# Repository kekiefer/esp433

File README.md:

# ESP433

KiCad source to build an ESP8266 WiFi to 433MHz ASK/OOK bridge

## How to Build One

This board is available on Oshpark: https://oshpark.com/shared_projects/5Debb7gg

The bom has been exported here as esp433.csv

## Key Components

* ESP12s - ESP8266 surface mount WiFi module
* Maxim MAX7044AKA+T - 300 ~ 450 MHz ASK/OOK RF transmitter
* Mean Well IRM-02-5 - AC to DC Power Supply 5V 2W
* PolyCase GS-2315 - Plug-in project enclosure

## More Information

A project writeup is available on hackaday.io: https://hackaday.io/project/63004-esp433-wifi-to-433mhz-bridge

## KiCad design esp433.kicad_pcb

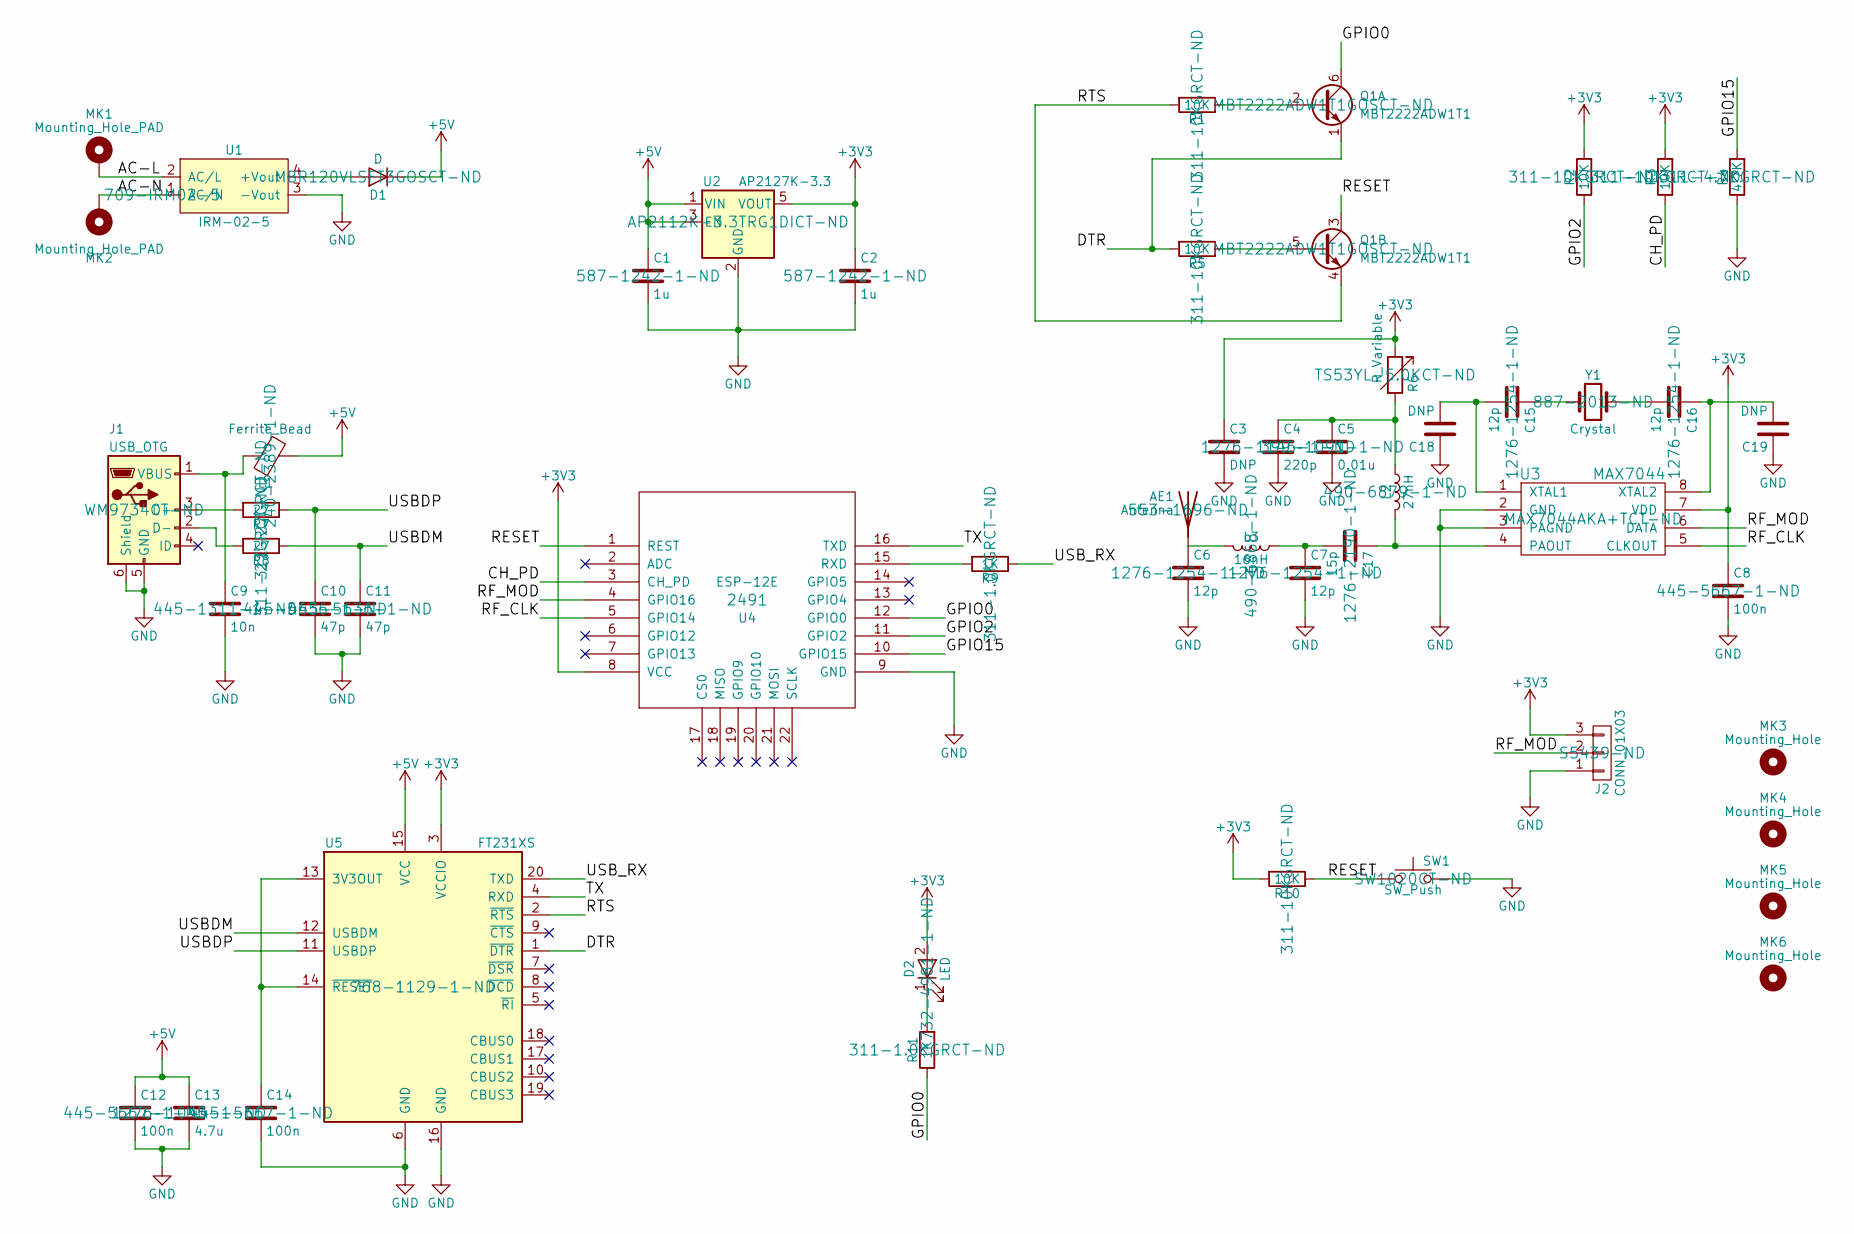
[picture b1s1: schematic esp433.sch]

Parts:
AE1: Antenna; W3127
C1, C2: 1u; C_0603
C3, C18, C19: DNP; C_0603
C4: 220p; C_0603
C5: 0.01u; C_0603
C6, C7, C15, C16: 12p; C_0603
C8, C12, C14: 100n; C_0603
C9: 10n; C_0603
C10, C11: 47p; C_0603
C13: 4.7u; C_0603
C17: 15p; C_0603
D1: D; D_SOD-123F
D2: LED; LED_0603
J1: USB_OTG; USB_Micro-B_Vertical_Molex-105133-0001
J2: CONN_01X03; Pin_Header_Angled_1x03
L1: Ferrite_Bead; L_0805
L2: 27nH; L_0603
L3: 16nH; L_0603
MK1, MK2: Mounting_Hole_PAD; SolderWirePad_single_2mmDrill
MK3, MK4, MK5, MK6: Mounting_Hole; MountingHole_3.2mm_M3
Q1: MBT2222ADW1T1; SOT-363_SC-70-6
R1, R2, R3, R5, R10: 10K; R_0603
R4: 4.7K; R_0603
R6: R_Variable; Potentiometer_Trimmer_Vishay_TS53YL
R7, R8: 27; R_0603
R9, R11: 1K; R_0603
SW1: SW_Push; SW_SPST_B3U-1000P
U1: IRM-02-5; ACDC-Converter_MeanWell-IRM-02-x
U2: AP2127K-3.3; SOT-23-5
U3: MAX7044; SOT-23-8
U4: ESP-12E; ESP-12E_SMD
U5: FT231XS; SSOP-20
Y1: Crystal; Crystal_HC49-U_Vertical

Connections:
+3V3: C2.1, C3.1, C8.1, D2.2 (A), J2.3, R2.2, R3.2, R6.1, R10.2, U2.5 (VOUT), U3.7 (VDD), U4.8 (VCC), U5.3 (VCCIO)
+5V: C1.1, C12.1, C13.1, D1.1 (K), L1.2, U2.1 (VIN), U2.3 (EN), U5.15 (VCC)
/AC-L: MK1.1, U1.2 (AC/L)
/AC-N: MK2.1, U1.1 (AC/N)
/CH_PD: R3.1, U4.3 (CH_PD)
/DTR: Q1.1 (E1), R5.2, U5.1 (~DTR)
/GPIO0: Q1.6 (C1), R11.1, U4.12 (GPIO0)
/GPIO2: R2.1, U4.11 (GPIO2)
/GPIO15: R4.2, U4.10 (GPIO15)
/RESET: Q1.3 (C2), R10.1, SW1.1, U4.1 (REST)
/RF_CLK: U3.5 (CLKOUT), U4.5 (GPIO14)
/RF_MOD: J2.2, U3.6 (DATA), U4.4 (GPIO16)
/RTS: Q1.4 (E2), R1.2, U5.2 (~RTS)
/TX: U4.16 (TXD), U5.4 (RXD)
/USBDM: C11.1, R8.1, U5.12 (USBDM)
/USBDP: C10.1, R7.1, U5.11 (USBDP)
/USB_RX: R9.1, U5.20 (TXD)
GND: C1.2, C2.2, C3.2, C4.2, C5.2, C6.2, C7.2, C8.2, C9.2, C10.2, C11.2, C12.2, C13.2, C14.2, C18.1, C19.1, J1.5 (GND), J1.6 (Shield), J2.1, R4.1, SW1.2, U1.3 (-Vout), U2.2 (GND), U3.2 (GND), U3.3 (PAGND), U4.9 (GND), U5.6 (GND), U5.16 (GND)
unnamed: AE1.1, C6.1, L3.2
unnamed: C4.1, C5.1, L2.1, R6.2
unnamed: C9.1, J1.1 (VBUS), L1.1
unnamed: C14.1, U5.13 (3V3OUT), U5.14 (~RESET)
unnamed: C15.1, Y1.1
unnamed: C15.2, C18.2, U3.1 (XTAL1)
unnamed: C16.1, C19.2, U3.8 (XTAL2)
unnamed: C16.2, Y1.2
unnamed: C17.1, L2.2, U3.4 (PAOUT)
unnamed: C7.1, C17.2, L3.1
unnamed: D1.2 (A), U1.4 (+Vout)
unnamed: D2.1 (K), R11.2
unnamed: J1.2 (D-), R8.2
unnamed: J1.3 (D+), R7.2
unnamed: Q1.2 (B1), R1.1
unnamed: Q1.5 (B2), R5.1
unnamed: R9.2, U4.15 (RXD)

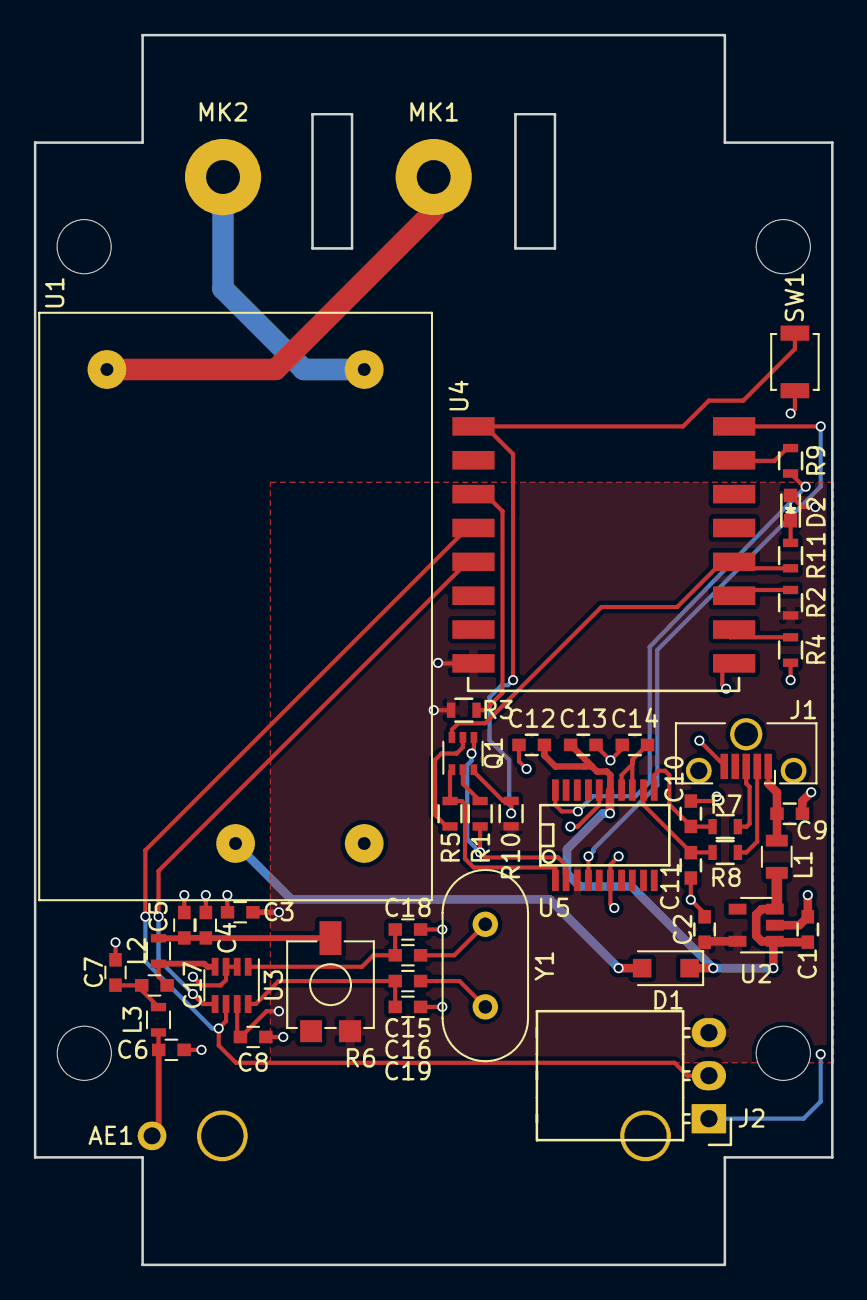
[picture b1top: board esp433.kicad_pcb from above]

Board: 2 copper layers, 47.1 x 72.6 mm, 52 parts (0 on the bottom side), 35 nets.

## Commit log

2018-02-04 Add footprint for ant-433-heth
2018-02-04 Add rf circuit
2018-02-04 Rearrange silk
2018-02-04 Rearrange filtering according to datasheet
2018-02-04 Correct hot/neutral labeling on power input
2018-02-23 Rework to fix oscillator and antenna circuit
2018-02-23 Add project readme and license
2018-02-23 Add note to readme about the project box used
2018-02-23 Fix footprint for D1
2018-02-23 Add bom file
2018-02-23 Add link to oshpark
2018-02-24 Add some dnp footprints for additional oscillator parallel capacitance
2018-02-24 Pick inductors specified by MAX7044 reference design
2018-02-24 More parts to match reference design
2018-02-24 Update BOM for recent component changes to match MAX7044 reference
2018-02-24 Updated netlist in pcb, no change to layout
2018-02-24 Update oshpark board link to r2
